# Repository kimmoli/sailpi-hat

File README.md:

sailpi-hat
==========

Sensors:

  - ADXL345 acceleration sensor (i2c 0x53)
  - BMP180 pressure sensor (i2c 0x77)
  - MCP9800 temperature sensor (i2c 0x4d)
  - MCP3021 AD converter (i2c 0x48)

Connectors:

X2
--

  - 1 +5V output
  - 2 +5V output
  - 3 GND
  - 4 GND
  - 5 shutdown input (connect to GND to shutdown)
  - 6 +12V input
  - 7 +12V input
  - 8 GND
  
X3
--

  - 1 optional analog input (R4B)
  - 2 GND
  - 3 Not connected
  - 4 SCL1
  - 5 SDA1
  - 6 Not connected
  - 7 +3.3V output
  - 8 GND

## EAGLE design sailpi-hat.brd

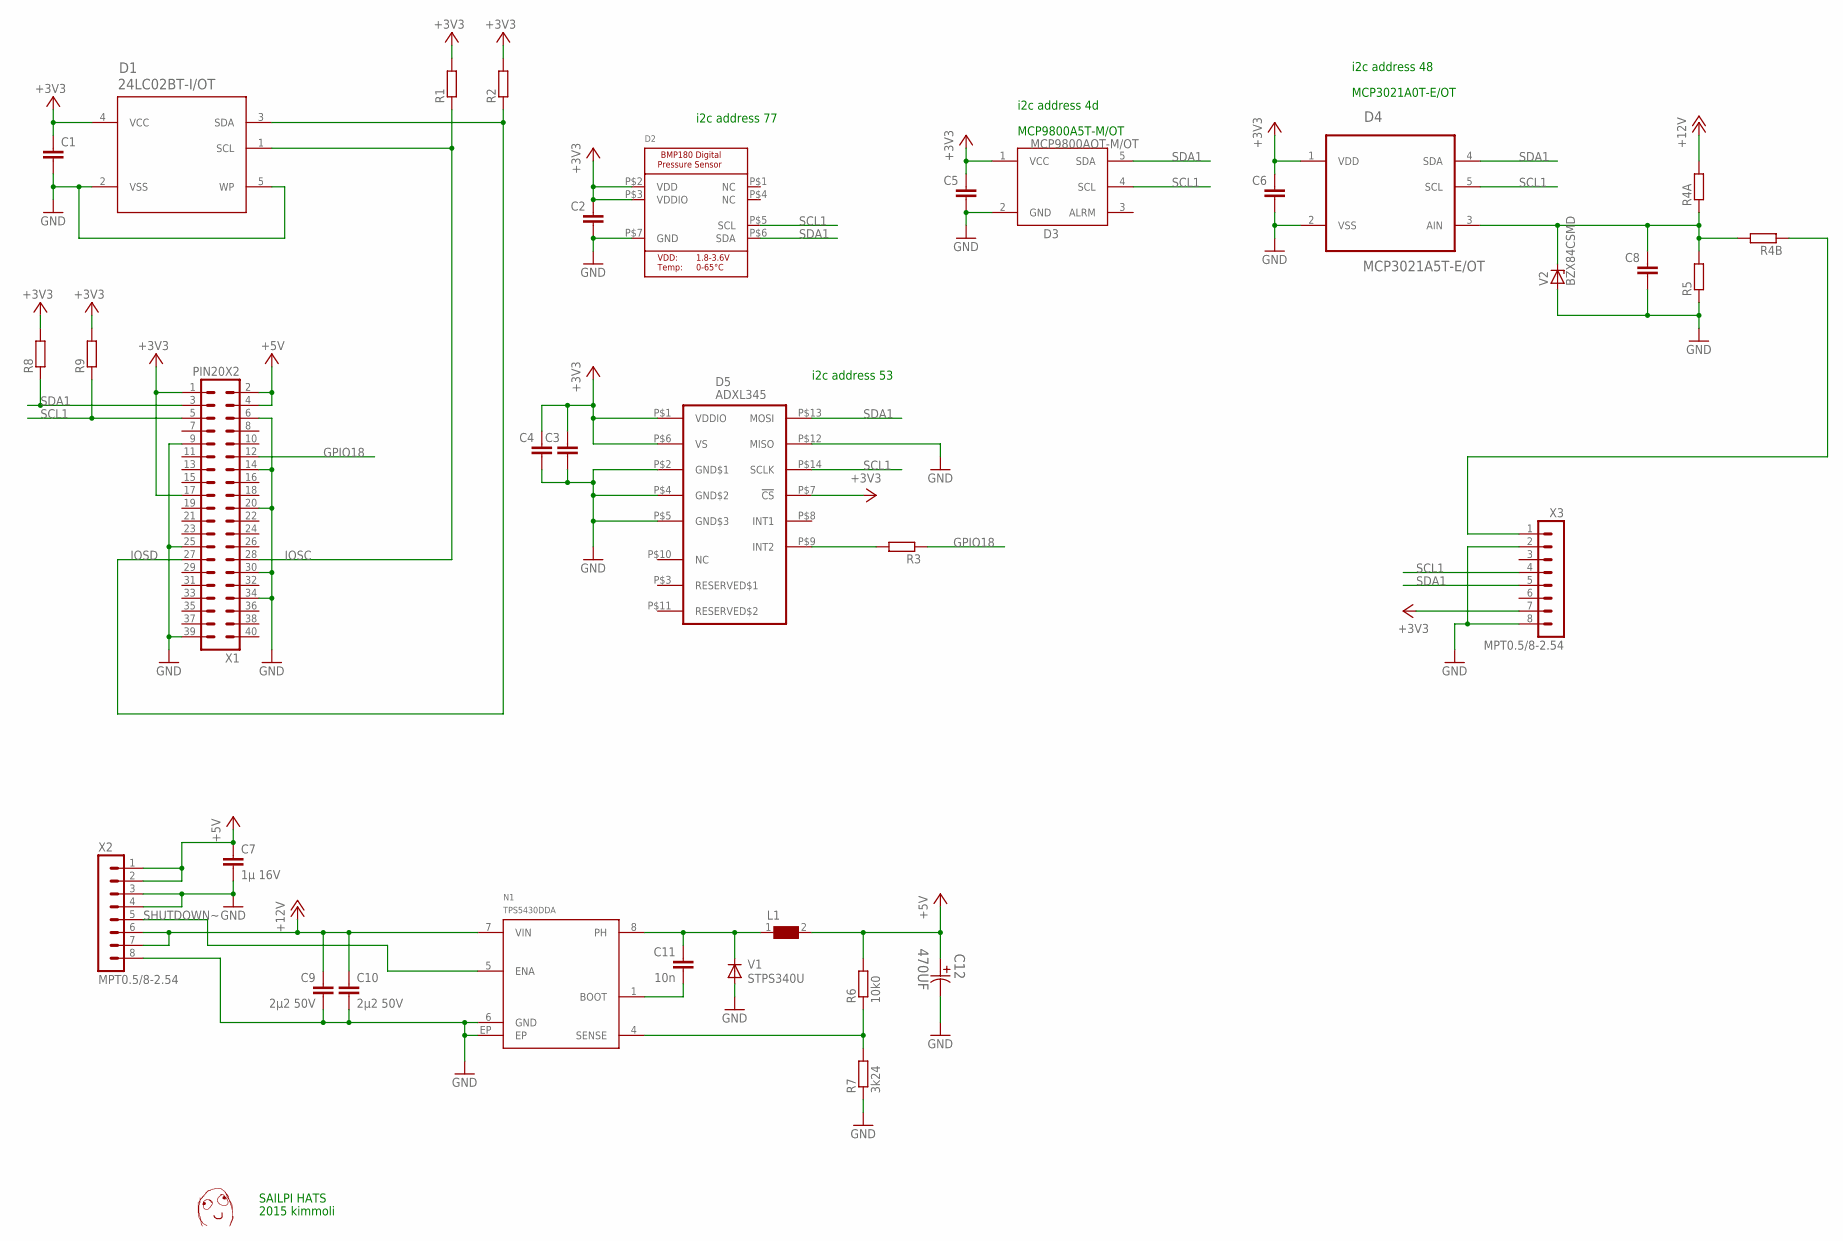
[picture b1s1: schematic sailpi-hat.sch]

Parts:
C1, C2, C3, C4, C5, C6, C8: CAP0603; C0603
C7: 1µ 16V; C0805
C9, C10: 2µ2 50V; C0805
C11: 10n; C0805
C12: 470UF; CAPAE1350X1400N
D1: 24LC02BT-I/OT; SOT95P280X145-5N
D2: BMP180EXT; BMP180_EXTENDED
D3: MCP9800AOT-M/OT; SOT23-5
D4: MCP3021A5T-E/OT; SOT95P270X145-5N
D5: ADXL345; LGA14
L1: WE-PD-7447709220_1260/1245/1280/1210; WE-PD_1260/1245/1280/1210
N1: TPS5430DDA; SOIC8-N-EP
R1, R2, R3, R4A, R4B, R5, R8, R9: RES0603; R0603
R6: 10k0; R0603
R7: 3k24; R0603
U$2: DAFUG
V1: STPS340U; SMB
V2: BZX84CSMD; TO236
X1: PIN20X2; PIN_20X2
X2, X3: MPT0.5/8-2.54

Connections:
+3V3: C1.1, C2.1, C3.1, C4.1, C5.1, C6.1, D1.4 (VCC), D2.P$2 (VDD), D2.P$3 (VDDIO), D3.1 (VCC), D4.1 (VDD), D5.P$1 (VDDIO), D5.P$6 (VS), D5.P$7 (!CS), R1.2, R2.2, R8.2, R9.2, X1.1, X1.17, X3.7
+5V: C7.1, C12.1, L1.2, R6.2, X1.2, X1.4, X2.1, X2.2
+12V: C9.1, C10.1, N1.7 (VIN), R4A.2, X2.6, X2.7
GND: C1.2, C2.2, C3.2, C4.2, C5.2, C6.2, C7.2, C8.2, C9.2, C10.2, C12.2, D1.2 (VSS), D1.5 (WP), D2.P$7 (GND), D3.2 (GND), D4.2 (VSS), D5.P$2 (GND$1), D5.P$4 (GND$2), D5.P$5 (GND$3), D5.P$12 (MISO), N1.6 (GND), N1.EP, R5.1, R7.1, V1.A, V2.A, X1.6, X1.9, X1.14, X1.20, X1.25, X1.30, X1.34, X1.39, X2.3, X2.4, X2.8, X3.2, X3.8
GPIO18: R3.1, X1.12
IOSC: D1.1 (SCL), R1.1, X1.28
IOSD: D1.3 (SDA), R2.1, X1.27
unnamed: D5.P$9 (INT2), R3.2
unnamed: R4B.1, X3.1
unnamed: C8.1, D4.3 (AIN), R4A.1, R4B.2, R5.2, V2.C
unnamed: C11.1, L1.1, N1.8 (PH), V1.C
unnamed: C11.2, N1.1 (BOOT)
unnamed: N1.4 (SENSE), R6.1, R7.2
SCL1: D2.P$5 (SCL), D3.4 (SCL), D4.5 (SCL), D5.P$14 (SCLK), R9.1, X1.5, X3.4
SDA1: D2.P$6 (SDA), D3.5 (SDA), D4.4 (SDA), D5.P$13 (MOSI), R8.1, X1.3, X3.5
SHUTDOWN~: N1.5 (ENA), X2.5

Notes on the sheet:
i2c address 53
i2c address 77
MCP9800A5T-M/OT
i2c address 4d
MCP3021A0T-E/OT
i2c address 48
SAILPI HATS
2015 kimmoli

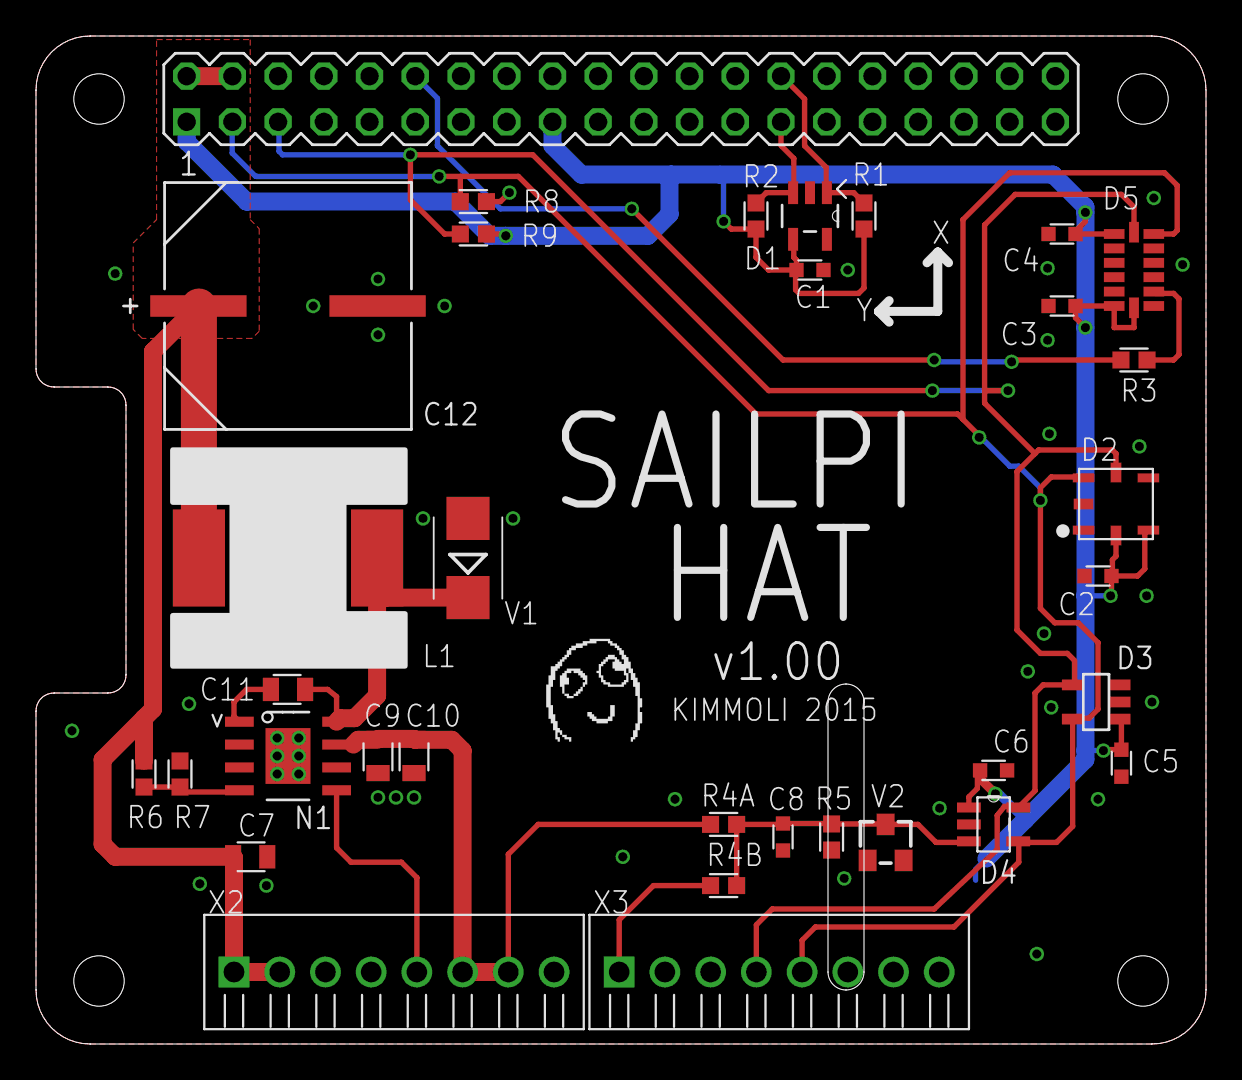
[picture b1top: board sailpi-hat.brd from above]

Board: 2 copper layers, 65.0 x 56.0 mm, 35 parts (0 on the bottom side), 16 nets.

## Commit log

2015-11-07 initial
2015-11-07 add schema and layout pdf, gerbers
